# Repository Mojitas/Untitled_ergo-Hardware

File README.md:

# untitled_ergo-Hardware, I don't really know what to call this yet.
A split BLE keyboard with thoughts put into thumb key placement.
Looks like a Kyria keyboard except for uniform 5mm staggering and specifically made for being wireless. 
Draws a lot of inspiration from Mitosis.

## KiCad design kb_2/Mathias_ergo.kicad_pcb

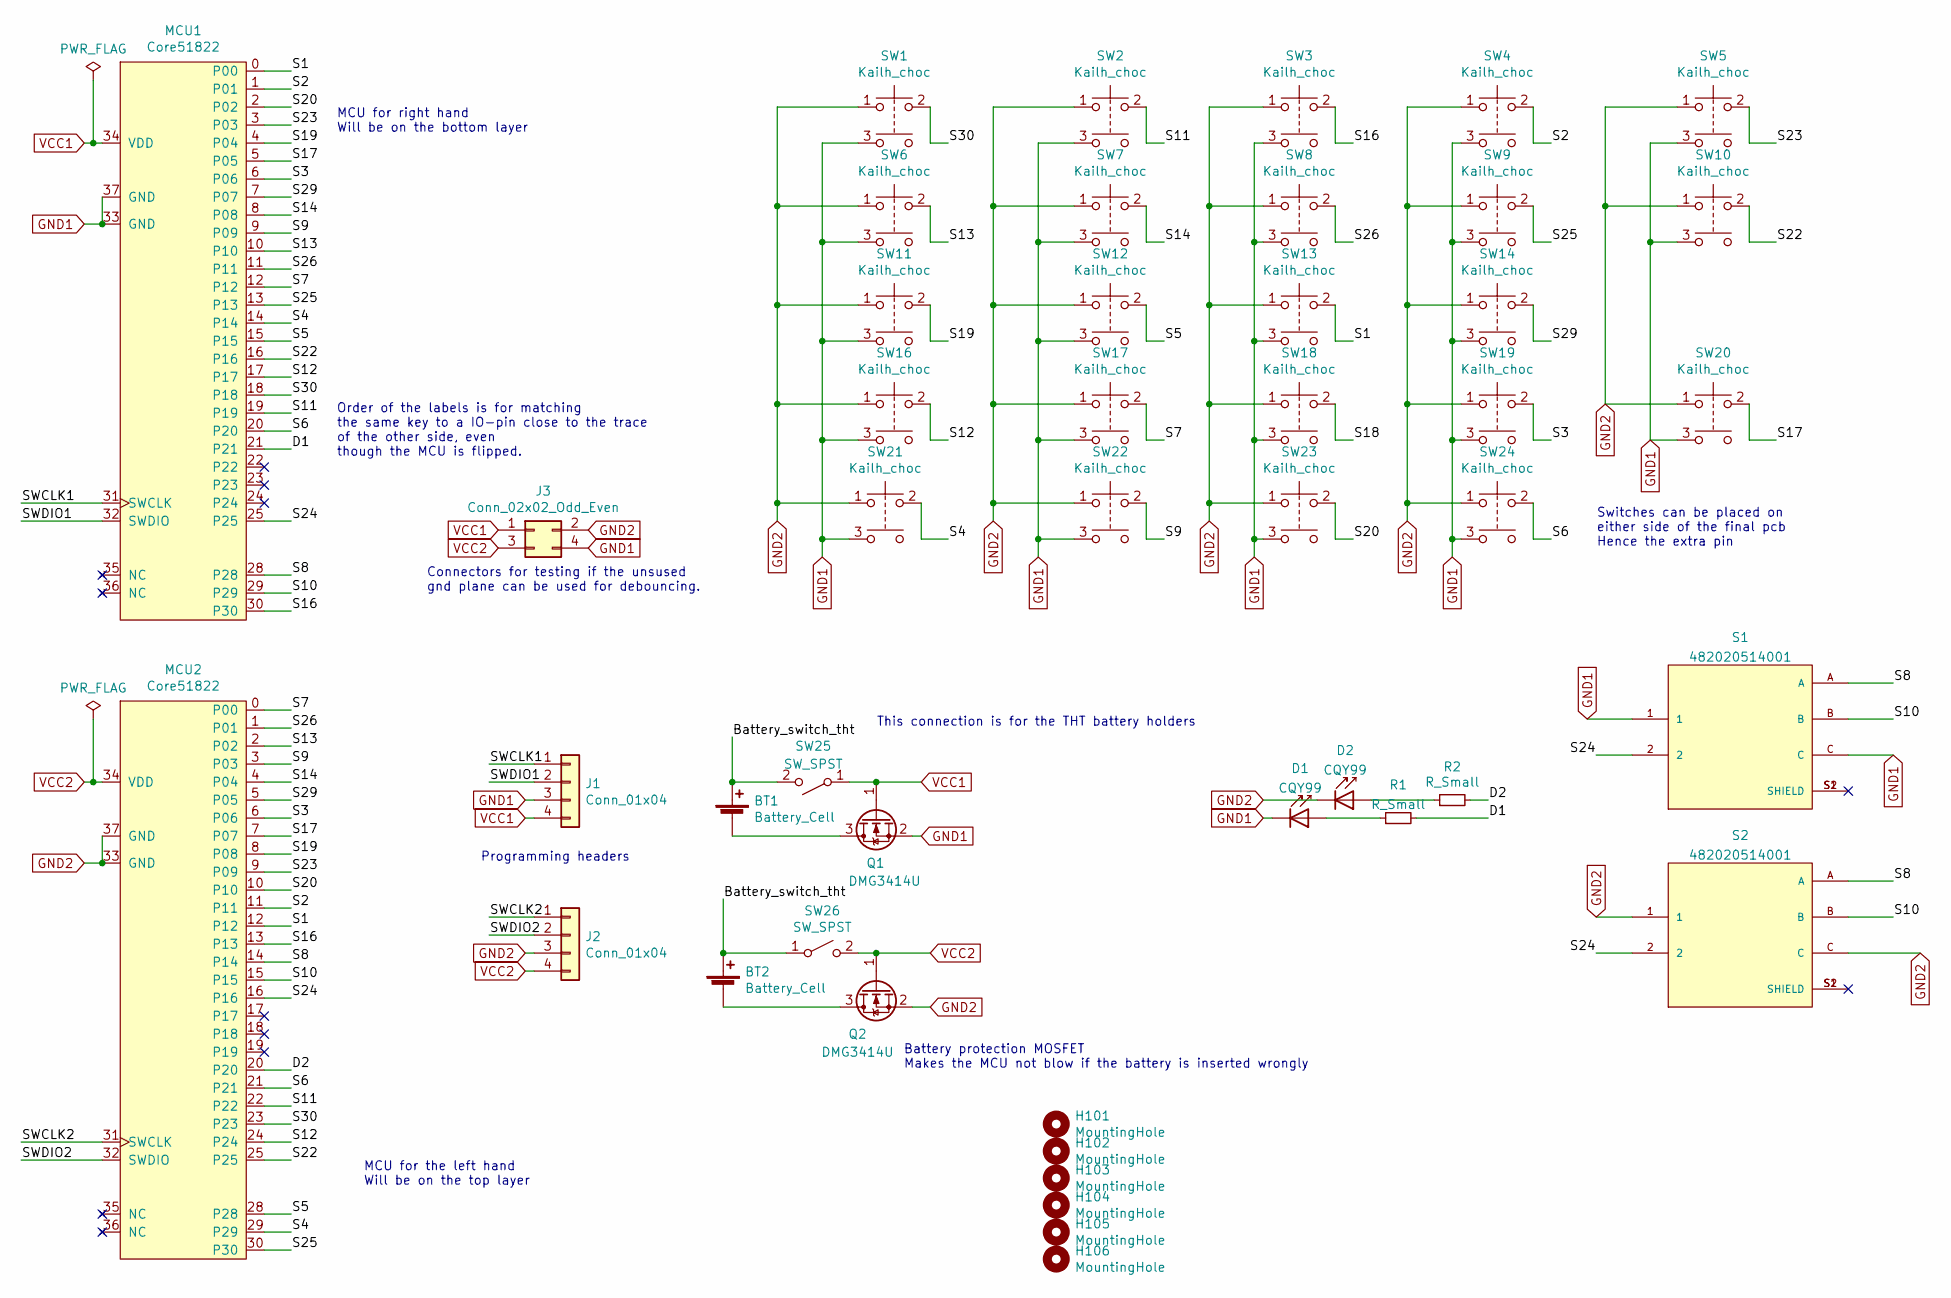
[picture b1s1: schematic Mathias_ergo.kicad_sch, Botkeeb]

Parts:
BT1, BT2: Battery_Cell; Battery_mod_tht
D1, D2: CQY99; D_0603_1608Metric
H101, H102, H103, H104, H105, H106: MountingHole; MountingHole_2.2mm_M2_Pad
J1, J2: Conn_01x04; PinHeader_1x04_P2.54mm_Horizontal
J3: Conn_02x02_Odd_Even; PinHeader_2x02_P2.54mm_Vertical
MCU1, MCU2: Core51822; YJ14015
Q1, Q2: DMG3414U; SOT-23
R1, R2: R_Small; R_0603_1608Metric
S1, S2: 482020514001; SW_482020514001; PARTREV 001.000
SW1, SW2, SW3, SW4, SW5, SW6, SW7, SW8, SW9, SW10, SW11, SW12, SW13, SW14, SW16, SW17, SW18, SW19, SW20, SW21, SW22, SW23, SW24: Kailh_choc; Kailh_low_profile
SW25, SW26: SW_SPST; PCM12SMTR

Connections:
/Battery_switch_tht: BT1.1 (+), BT2.1 (+), SW25.2 (B), SW26.1 (A)
/D1: MCU1.21, R1.2
/D2: MCU2.20, R2.2
/S1: MCU1.0, MCU2.12, SW13.2
/S2: MCU1.1, MCU2.11, SW4.2
/S3: MCU1.6, MCU2.6, SW19.2
/S4: MCU1.14, MCU2.29, SW21.2
/S5: MCU1.15, MCU2.28, SW12.2
/S6: MCU1.20, MCU2.21, SW24.2
/S7: MCU1.12, MCU2.0, SW17.2
/S8: MCU1.28, MCU2.14, S1.A, S2.A
/S9: MCU1.9, MCU2.3, SW22.2
/S10: MCU1.29, MCU2.15, S1.B, S2.B
/S11: MCU1.19, MCU2.22, SW2.2
/S12: MCU1.17, MCU2.24, SW16.2
/S13: MCU1.10, MCU2.2, SW6.2
/S14: MCU1.8, MCU2.4, SW7.2
/S16: MCU1.30, MCU2.13, SW3.2
/S17: MCU1.5, MCU2.7, SW20.2
/S19: MCU1.4, MCU2.8, SW11.2
/S20: MCU1.2, MCU2.10, SW23.2
/S22: MCU1.16, MCU2.25, SW10.2
/S23: MCU1.3, MCU2.9, SW5.2
/S24: MCU1.25, MCU2.16, S1.2, S2.2
/S25: MCU1.13, MCU2.30, SW9.2
/S26: MCU1.11, MCU2.1, SW8.2
/S29: MCU1.7, MCU2.5, SW14.2
/S30: MCU1.18, MCU2.23, SW1.2
/SWCLK1: J1.1, MCU1.31 (SWCLK)
/SWCLK2: J2.1, MCU2.31 (SWCLK)
/SWDIO1: J1.2, MCU1.32 (SWDIO)
/SWDIO2: J2.2, MCU2.32 (SWDIO)
GND1: D1.1 (K), J1.3, J3.4, MCU1.33 (GND), MCU1.37 (GND), Q1.2 (S), S1.1, S1.C, SW1.3, SW2.3, SW3.3, SW4.3, SW5.3, SW6.3, SW7.3, SW8.3, SW9.3, SW10.3, SW11.3, SW12.3, SW13.3, SW14.3, SW16.3, SW17.3, SW18.3, SW19.3, SW20.3, SW21.3, SW22.3, SW23.3, SW24.3
GND2: D2.1 (K), J2.3, J3.2, MCU2.33 (GND), MCU2.37 (GND), Q2.2 (S), S2.1, S2.C, SW1.1, SW2.1, SW3.1, SW4.1, SW5.1, SW6.1, SW7.1, SW8.1, SW9.1, SW10.1, SW11.1, SW12.1, SW13.1, SW14.1, SW16.1, SW17.1, SW18.1, SW19.1, SW20.1, SW21.1, SW22.1, SW23.1, SW24.1
unnamed: BT1.2 (-), Q1.3 (D)
unnamed: BT2.2 (-), Q2.3 (D)
unnamed: D1.2 (A), R1.1
unnamed: D2.2 (A), R2.1
VCC1: J1.4, J3.1, MCU1.34 (VDD), Q1.1 (G), SW25.1 (A)
VCC2: J2.4, J3.3, MCU2.34 (VDD), Q2.1 (G), SW26.2 (B)

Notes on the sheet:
MCU for the left hand Will be on the top layer
MCU for right hand Will be on the bottom layer
This connection is for the THT battery holders
Connectors for testing if the unsused gnd plane can be used for debouncing.
Switches can be placed on either side of the final pcb Hence the extra pin
Order of the labels is for matching the same key to a IO-pin close to the trace of the other side, even though the MCU is flipped.
Battery protection MOSFET Makes the MCU not blow if the battery is inserted wrongly
Programming headers

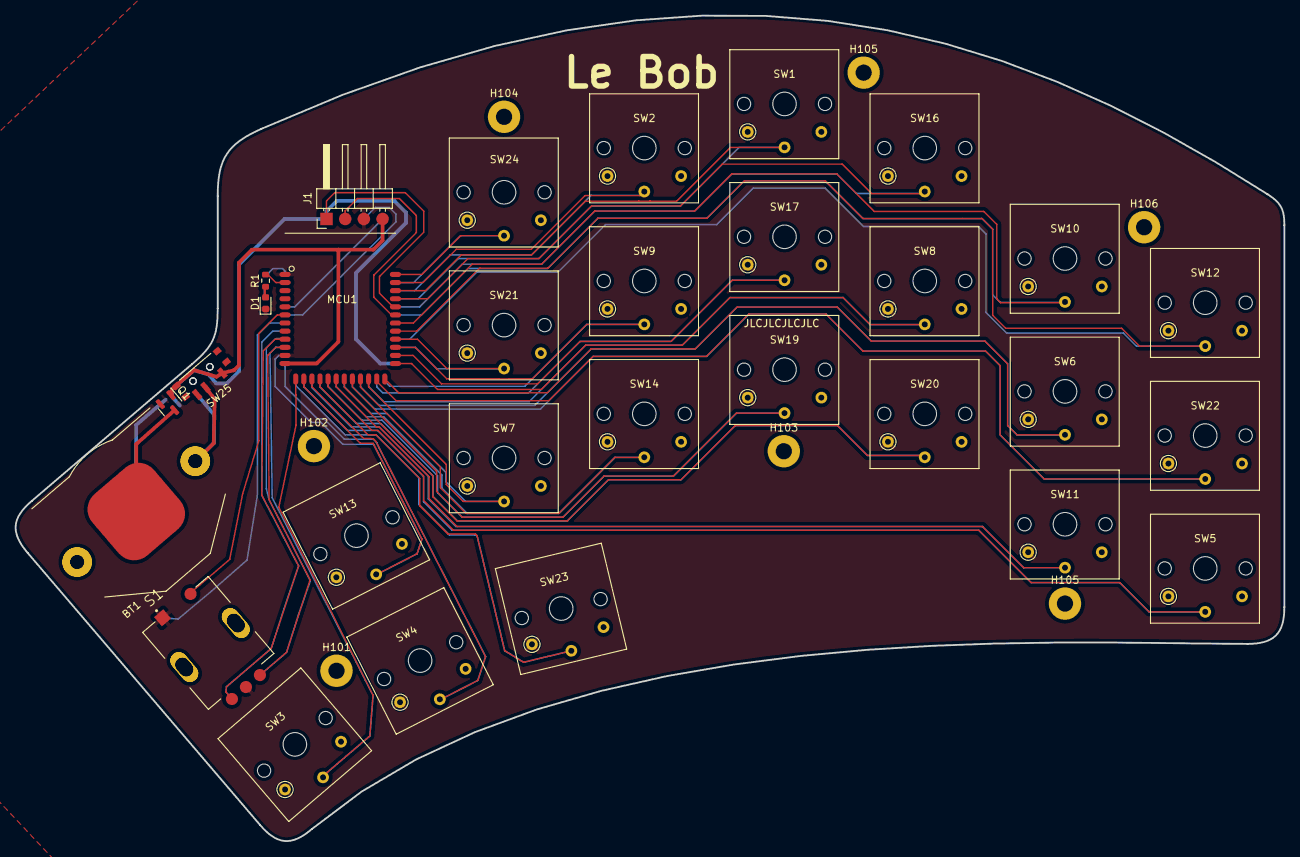
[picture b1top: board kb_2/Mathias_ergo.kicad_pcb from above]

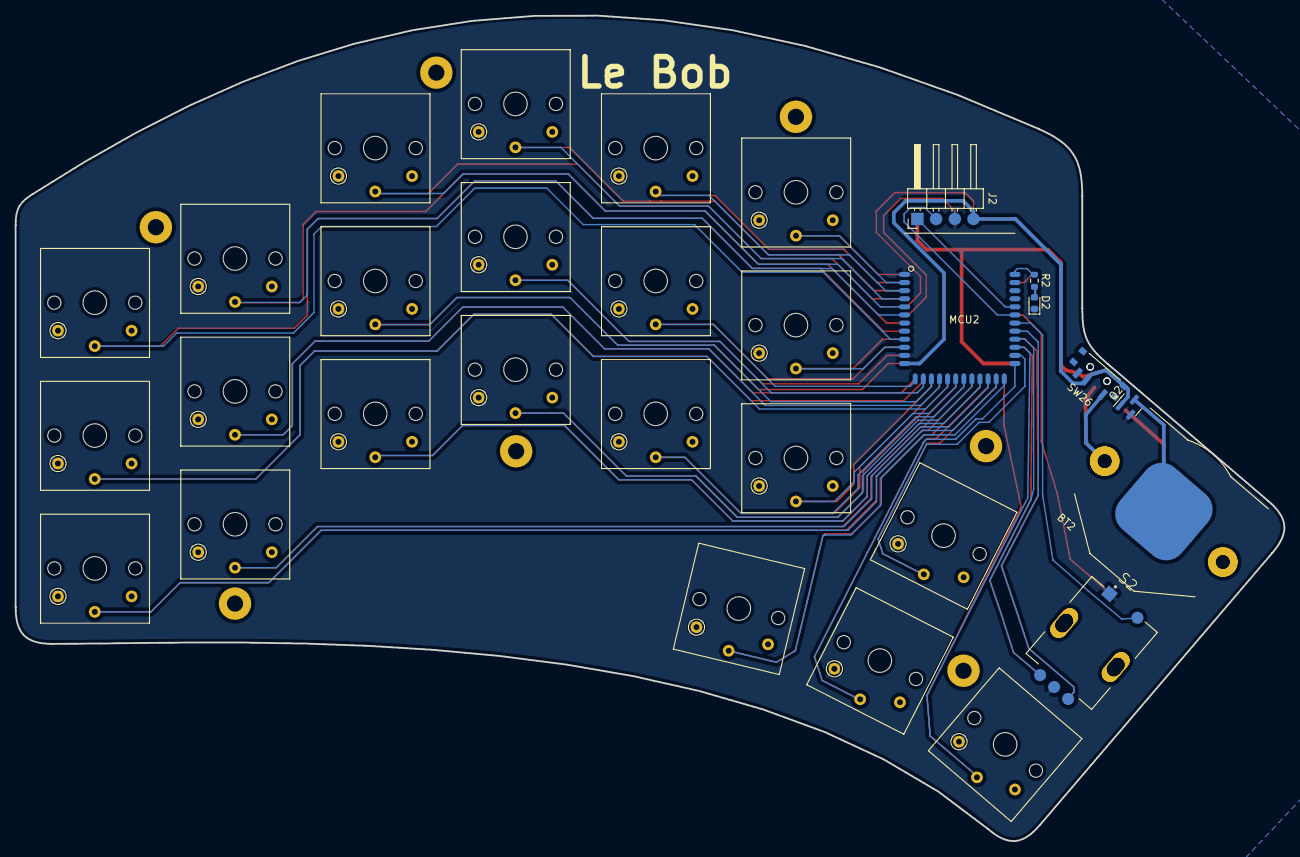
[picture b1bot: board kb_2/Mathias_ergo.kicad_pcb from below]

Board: 2 copper layers, 172.3 x 112.1 mm, 45 parts (8 on the bottom side), 40 nets.

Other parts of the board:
H105#2: MountingHole; MountingHole_2.2mm_M2_Pad

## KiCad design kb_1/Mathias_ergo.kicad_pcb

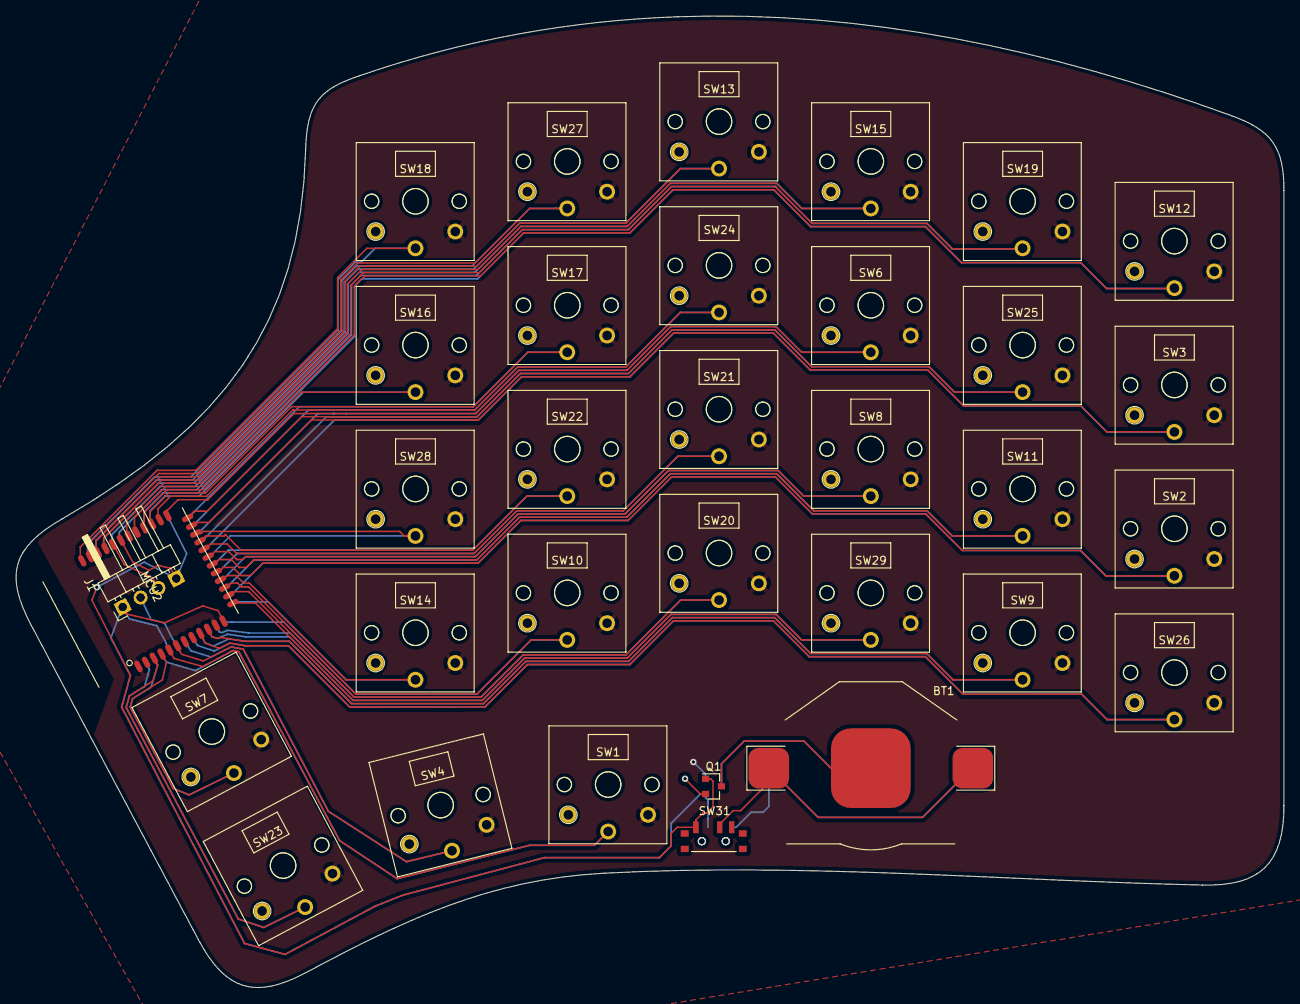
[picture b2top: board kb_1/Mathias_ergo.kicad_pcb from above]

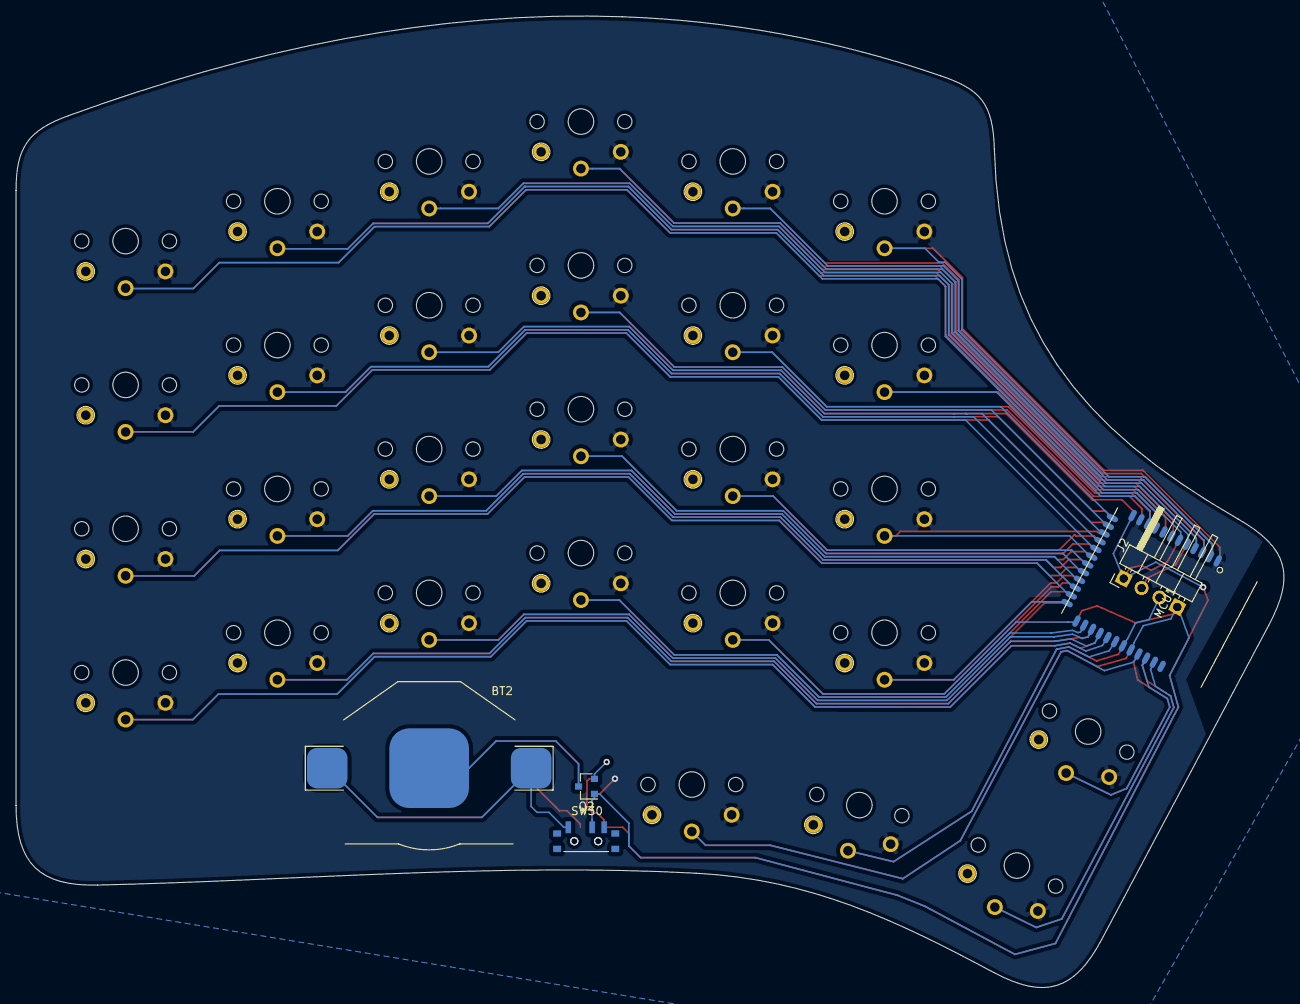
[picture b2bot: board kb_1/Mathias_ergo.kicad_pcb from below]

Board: 2 copper layers, 159.1 x 121.9 mm, 38 parts (5 on the bottom side), 40 nets.

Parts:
BT1, BT2: Battery_Cell; Battery_mod
J1, J2: Conn_01x04; PinHeader_1x04_P2.54mm_Horizontal
MCU1, MCU2: Core51822; YJ14015
Q1, Q2: DMG3414U; SOT-23
SW1, SW2, SW3, SW4, SW6, SW7, SW8, SW9, SW10, SW11, SW12, SW13, SW14, SW15, SW16, SW17, SW18, SW19, SW20, SW21, SW22, SW23, SW24, SW25, SW26, SW27, SW28, SW29: SW_Push_Dual; Kailh_low_profile
SW30, SW31: SW_SPST; PCM12SMTR

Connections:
/S1: MCU1.24, MCU2.17, SW15.2
/S2: MCU1.25, MCU2.16, SW19.2
/S3: MCU1.5, MCU2.7, SW22.2
/S4: MCU1.13, MCU2.30, SW29.2
/S5: MCU1.14, MCU2.29, SW9.2
/S6: MCU1.19, MCU2.22, SW23.2
/S7: MCU1.11, MCU2.1, SW10.2
/S8: MCU1.0, MCU2.12, SW24.2
/S9: MCU1.8, MCU2.4, SW11.2
/S11: MCU1.18, MCU2.23, SW7.2
/S12: MCU1.16, MCU2.25, SW4.2
/S13: MCU1.9, MCU2.3, SW2.2
/S14: MCU1.7, MCU2.5, SW8.2
/S15: MCU1.1, MCU2.11, SW6.2
/S16: MCU1.23, MCU2.18, SW13.2
/S17: MCU1.4, MCU2.8, SW28.2
/S18: MCU1.29, MCU2.14, SW16.2
/S19: MCU1.3, MCU2.9, SW3.2
/S20: MCU1.30, MCU2.13, SW17.2
/S21: MCU1.21, MCU2.20, SW18.2
/S22: MCU1.15, MCU2.28, SW26.2
/S23: MCU1.2, MCU2.10, SW25.2
/S24: MCU1.22, MCU2.19, SW27.2
/S25: MCU1.12, MCU2.0, SW20.2
/S26: MCU1.10, MCU2.2, SW14.2
/S28: MCU1.28, MCU2.15, SW12.2
/S29: MCU1.6, MCU2.6, SW21.2
/S30: MCU1.17, MCU2.24, SW1.2
/SWCLK1: J1.1, MCU1.31
/SWCLK2: J2.2, MCU2.31
/SWDIO1: J1.2, MCU1.32
/SWDIO2: J2.1, MCU2.32
GND1: J1.3, MCU1.33, MCU1.37, Q1.2, SW1.3, SW2.3, SW3.3, SW4.3, SW6.3, SW7.3, SW8.3, SW9.3, SW10.3, SW11.3, SW12.3, SW13.3, SW14.3, SW15.3, SW16.3, SW17.3, SW18.3, SW19.3, SW20.3, SW21.3, SW22.3, SW23.3, SW24.3, SW25.3, SW26.3, SW27.3, SW28.3, SW29.3
GND2: J2.3, MCU2.33, MCU2.37, Q2.2, SW1.1, SW2.1, SW3.1, SW4.1, SW6.1, SW7.1, SW8.1, SW9.1, SW10.1, SW11.1, SW12.1, SW13.1, SW14.1, SW15.1, SW16.1, SW17.1, SW18.1, SW19.1, SW20.1, SW21.1, SW22.1, SW23.1, SW24.1, SW25.1, SW26.1, SW27.1, SW28.1, SW29.1
unnamed: BT1.1, SW31.2
unnamed: BT1.2, Q1.3
unnamed: BT2.1, SW30.1
unnamed: BT2.2, Q2.3
VCC1: J1.4, MCU1.34, Q1.1, SW31.1
VCC2: J2.4, MCU2.34, Q2.1, SW30.2

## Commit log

2020-03-27 Cad files added
2020-03-27 Changed to more logical names
2020-03-27 Changed names
2020-06-09 Kicad folder with schematic and board layout added
2020-06-16 Changed and updated the pcb
    Libraries and footprints added
2020-06-16 Changed names
    Updated names and added board outline
2020-06-16 Replaced old files
2020-06-16 replaced test print file
2020-10-10 Newer design that I like more
2020-11-13 added silkscreen
2020-11-13 some author things
2020-11-17 Design rules check
2020-11-17 Added defined positions for mounting holes
2020-11-17 Some fixes on outline
2020-11-24 New outline
    Fixed the board outline,
    thumb buttons positions,
    battery footprint,
    gnd pours
2021-01-29 Send to factory version
2021-01-31 Exported gerbers
2021-02-20 Added image
2021-02-20 Added BoM for 1 either half
2021-02-20 Added BoM
2021-02-20 Added more clearances between traces
2021-05-26 added last
2022-12-27 pushing before wipe
2022-12-27 Adding before wipe
